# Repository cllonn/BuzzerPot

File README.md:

# Speaker PCB Project  
A PCB designed to drive a speaker using an SC8002B amplifier

## Project Overview  
This project is built for easy access to amplified sound output, designed using an SC8002B amplifier and a potentiometer to adjust volume. It operates within a 3.3V to 5V range for flexibility with different power sources.

## Features  
- SC8002B Audio Amplifier – Provides 1.2W output at 8Ω for clear sound.  
- Speaker Compatibility – Works with an 8Ω, 1W speaker (INGHAi GSPK2307P-8R1W).  
- Potentiometer Control – Uses a 3386P Long Neck with a knob for easy volume adjustment.  
- Compact PCB Layout – Optimized for space efficiency while maintaining performance.

## Circuit Schematic  

## PCB Layout  

## Usage  
To use the board:  
1- Connect Power – Attach a power source (3.3V - 5V)
2- Adjust Volume – Use the potentiometer to control the speaker output 
3- Apply an Audio Signal – Feed a signal from a microcontroller or an external sourc
4- Test Output Levels – Verify speaker performance at different power levels

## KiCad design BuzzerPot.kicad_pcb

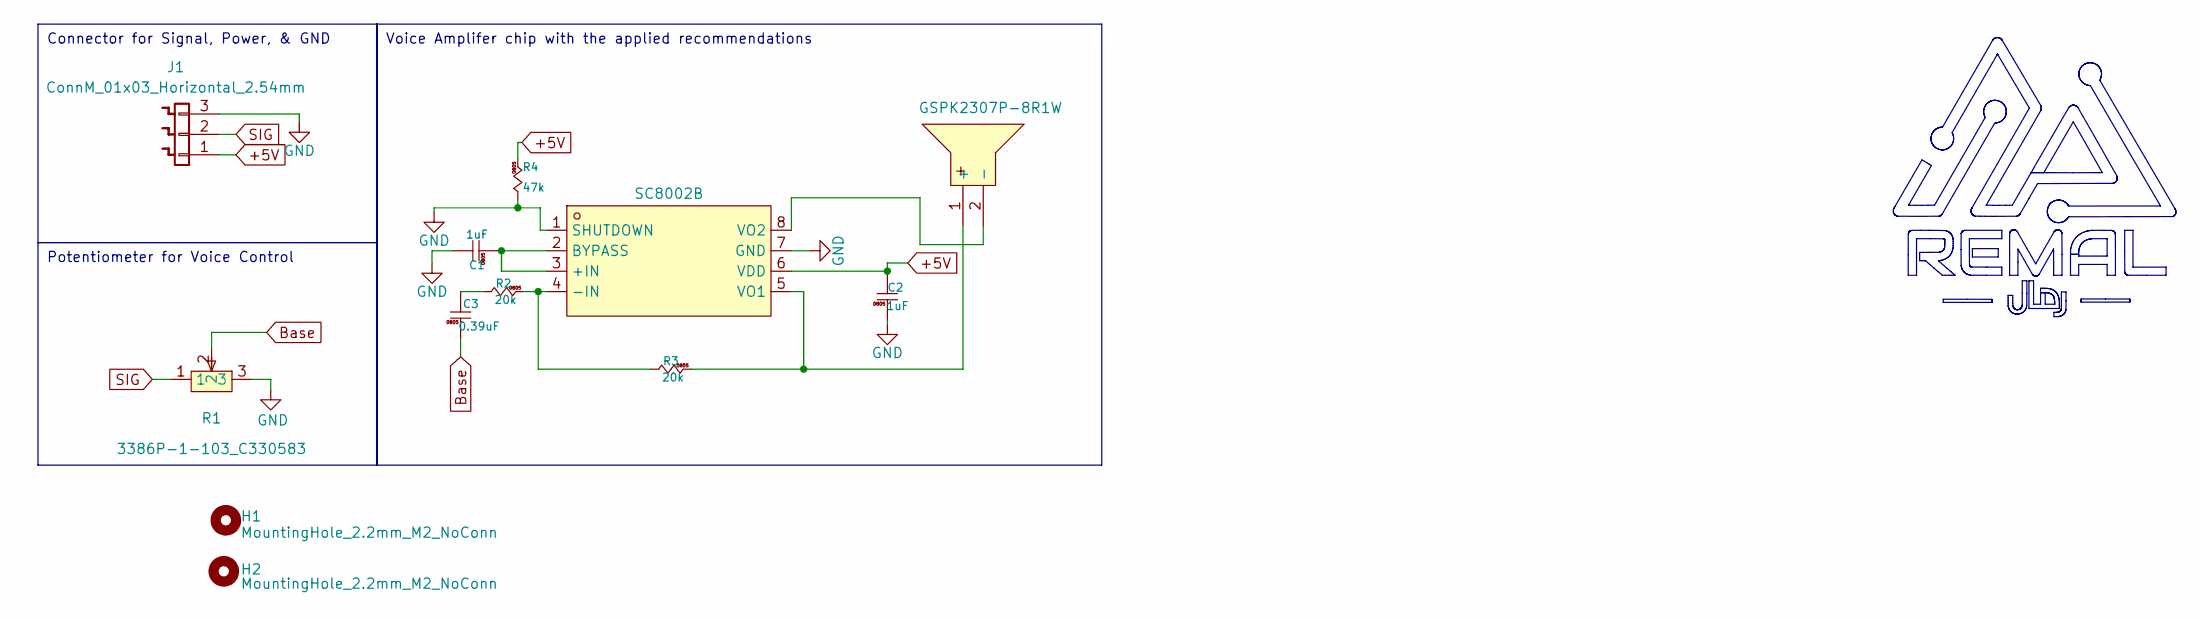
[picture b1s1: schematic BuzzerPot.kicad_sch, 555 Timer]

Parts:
C1, C2: 1uF; C_0805_2012m
C3: 0.39uF; C_0805_2012m
H1, H2: MountingHole_2.2mm_M2_NoConn
J1: ConnM_01x03_Horizontal_2.54mm; PinHeader_1x03_P2.54mm_Horizontal
R1: 3386P-1-103_C330583; RES-ADJ-TH_3P-L9.5-W9.5-P2.50-L_3386P; LCSC Part C330583
R2, R3: 20k; R_0805_2012m
R4: 47k; R_0805_2012m
SPK1: GSPK2307P-8R1W; SPK-TH_BD23.0-P10.00-D0.8-L-RD; LCSC Part C530531
U1: SC8002B; SOP-8_L4.9-W3.9-P1.27-LS6.0-BL; LCSC Part C82124

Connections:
+5V: C2.2, J1.1, R4.2, U1.6 (VDD)
Base: C3.1, R1.2
GND: C1.2, C2.1, J1.3, R1.3, R4.1, U1.1 (SHUTDOWN), U1.7 (GND)
unnamed: C3.2, R2.1
unnamed: R3.2, SPK1.1 (+), U1.5 (VO1)
unnamed: SPK1.2 (-), U1.8 (VO2)
unnamed: C1.1, U1.2 (BYPASS), U1.3 (+IN)
unnamed: R2.2, R3.1, U1.4 (-IN)
SIG: J1.2, R1.1

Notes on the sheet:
Connector for Signal, Power, & GND
Potentiometer for Voice Control
Voice Amplifer chip with the applied recommendations

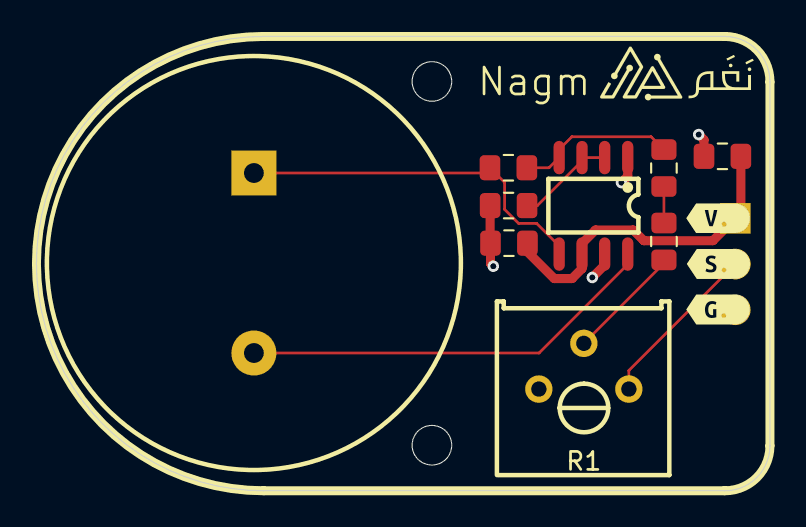
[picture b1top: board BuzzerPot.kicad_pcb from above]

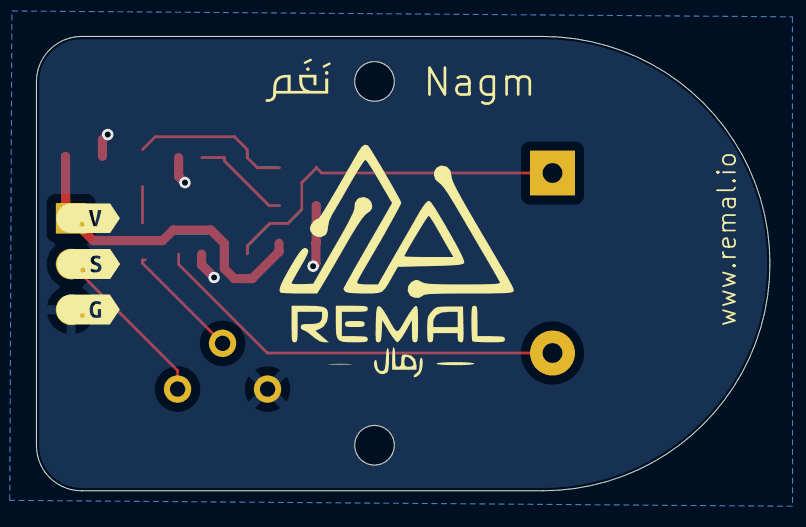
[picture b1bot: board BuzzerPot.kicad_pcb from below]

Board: 2 copper layers, 40.7 x 25.2 mm, 18 parts (3 on the bottom side), 9 nets.

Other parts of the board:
kibuzzard-67CEDACD: G***; kibuzzard-67CEDACD
kibuzzard-67CEDAF1: G***; kibuzzard-67CEDAF1
kibuzzard-67D2B7CA: G***; kibuzzard-67D2B7CA
kibuzzard-67D32B2A: G***; kibuzzard-67D32B2A
kibuzzard-67D32B2F: G***; kibuzzard-67D32B2F
kibuzzard-67D32B23: G***; kibuzzard-67D32B23

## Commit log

2025-03-06 Added BuzzerPot KiCad project
2025-03-06 README.md
2025-03-11 Updated: Replaced Buzzer with Speaker
2025-03-11 Updated Version 2
2025-03-13 Last Changes: Added Logo and Name
2025-03-13 Updated: Remal Golden Standard Recheck
2025-03-19 Last Update: Inserted two Mounting Holes M2
